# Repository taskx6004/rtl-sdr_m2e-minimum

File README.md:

# rtl-sdr_m2e-minimum
Minimum hardware design for RTL-SDR in m.2 key-e form

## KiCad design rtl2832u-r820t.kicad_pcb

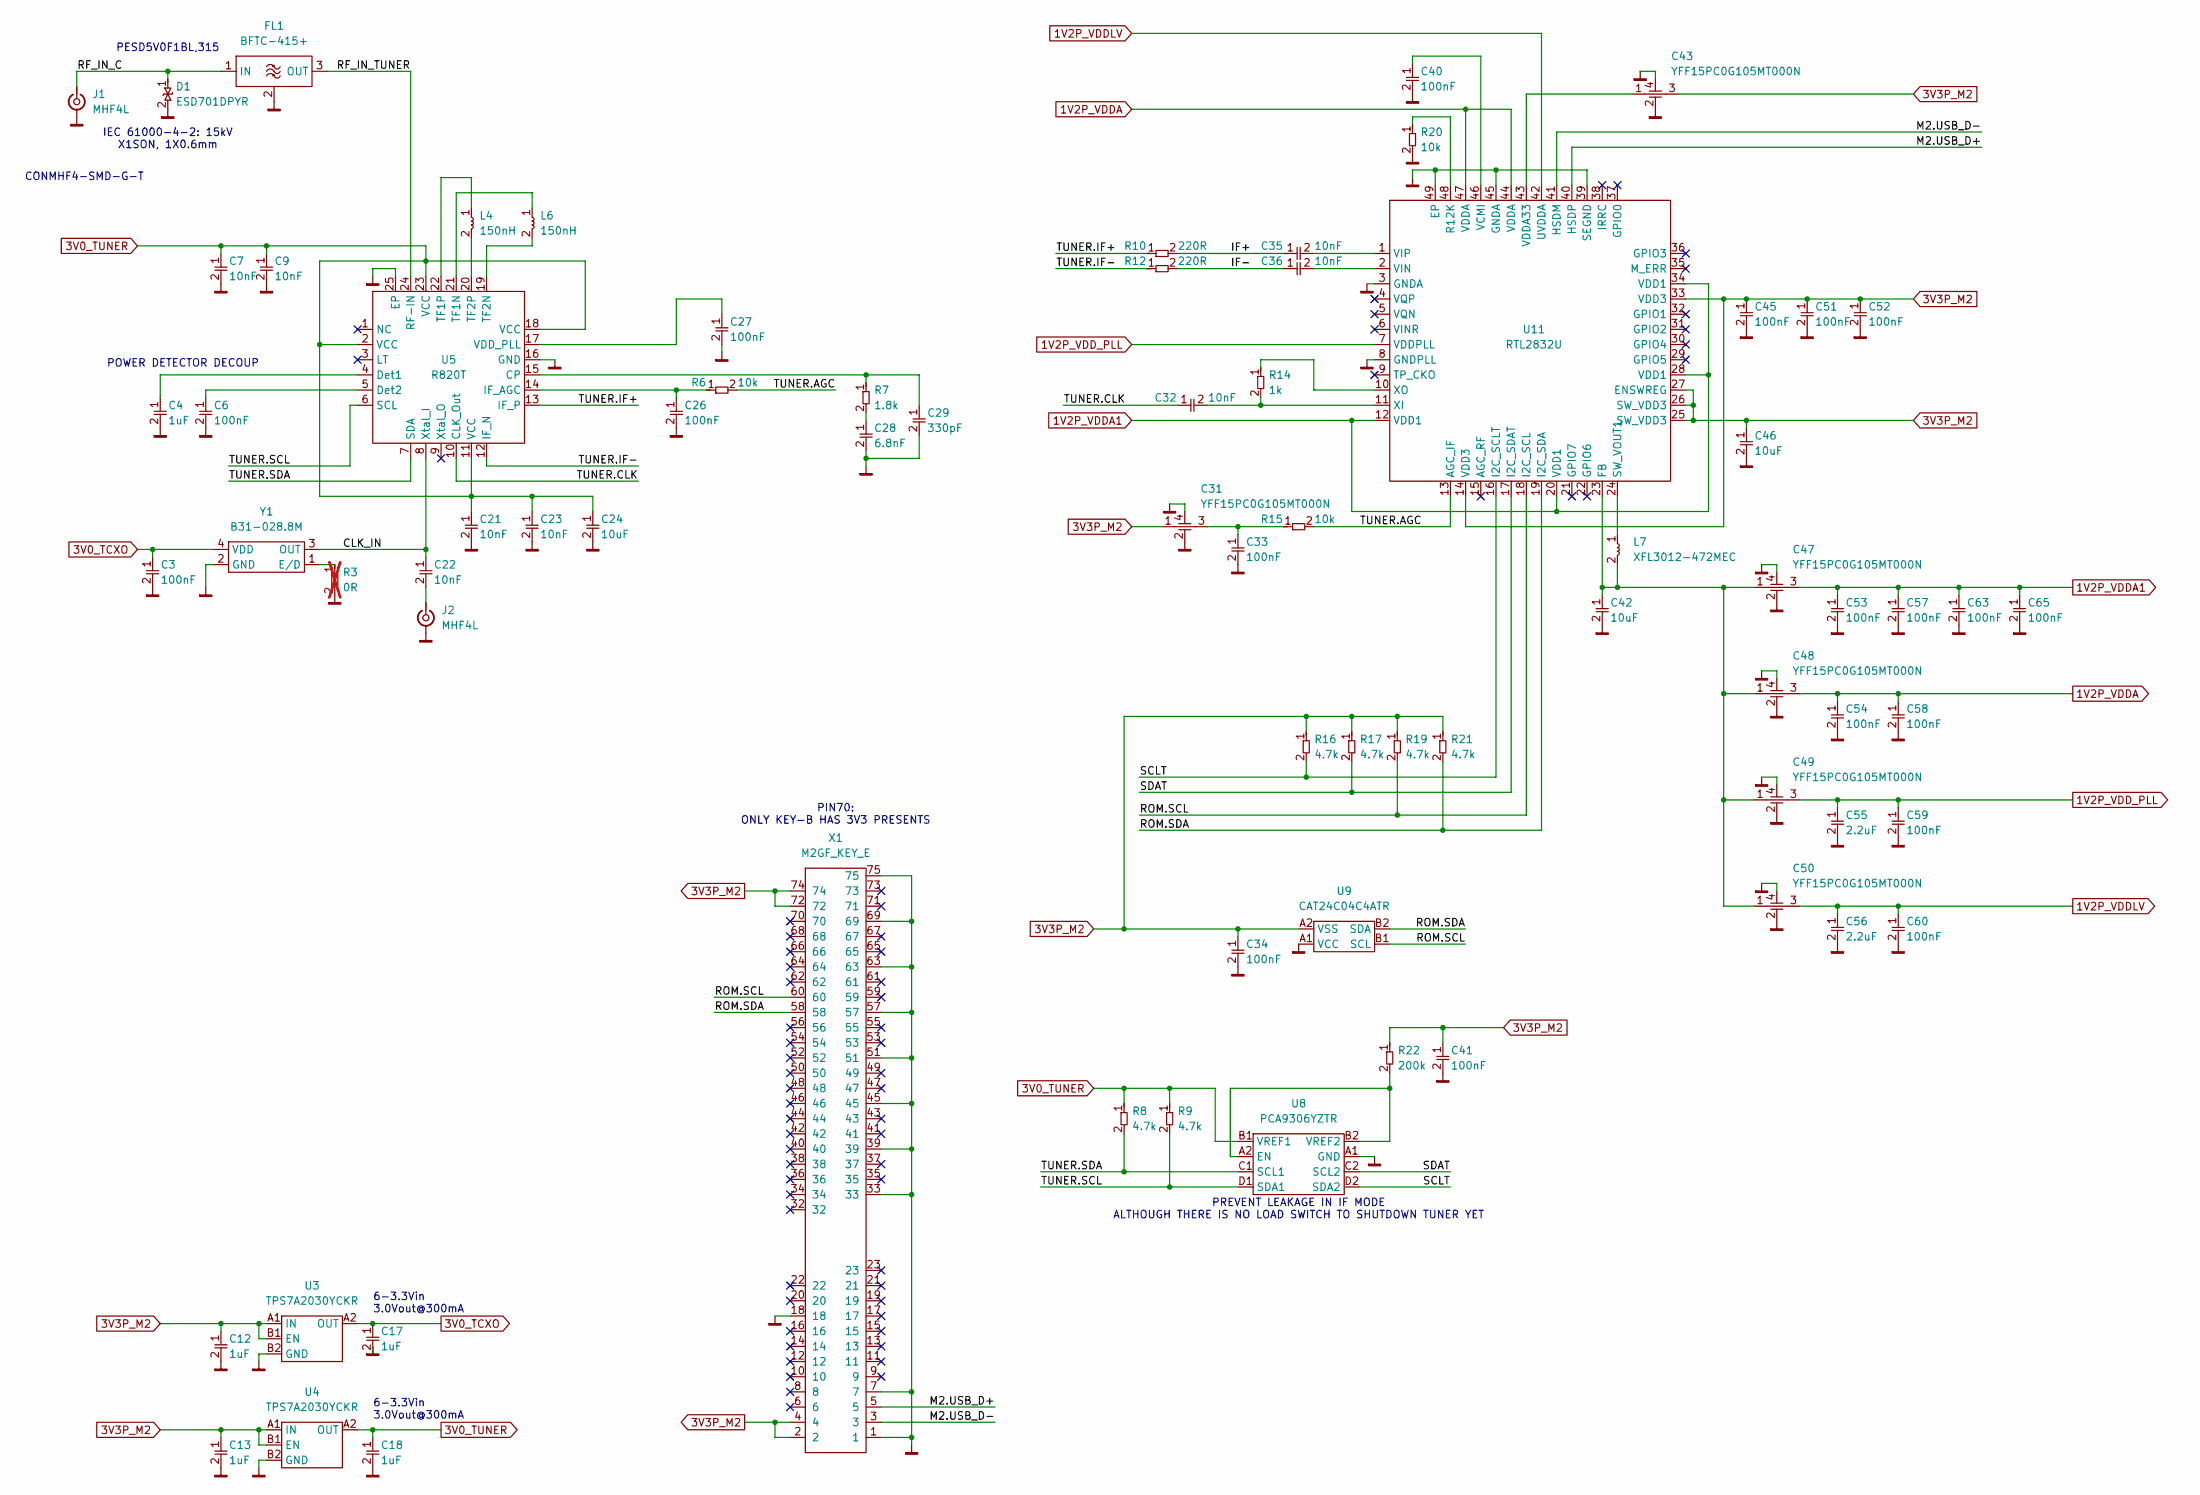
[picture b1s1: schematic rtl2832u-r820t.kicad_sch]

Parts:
C3, C6, C26, C27, C33, C34, C40, C41, C45, C51, C52, C53, C54, C57, C58, C59, C60, C63, C65: 100nF; C_0201
C4, C12, C13, C17, C18: 1uF; C_0201
C7, C9, C21, C22, C23, C32, C35, C36: 10nF; C_0201
C24, C42, C46: 10uF; C_0402
C28: 6.8nF; C_0201
C29: 330pF; C_0201
C31, C43, C47, C48, C49, C50: YFF15PC0G105MT000N
C55, C56: 2.2uF; C_0402
D1: ESD701DPYR
FL1: BFTC-415+
J1, J2: MHF4L
L4, L6: 150nH; L_0402
L7: XFL3012-472MEC
R3: 0R; R_0201; not fitted
R6, R15, R20: 10k; R_0201
R7: 1.8k; R_0201
R8, R9, R16, R17, R19, R21: 4.7k; R_0201
R10, R12: 220R; R_0201
R14: 1k; R_0201
R22: 200k; R_0201
U3, U4: TPS7A2030YCKR; TPS7A2018PYCKR
U5: R820T; R820T2
U8: PCA9306YZTR
U9: CAT24C04C4ATR; SN74LVC1G06DSFR
U11: RTL2832U
X1: M2GF_KEY_E; M2GF_KEY_E_2230
Y1: B31-028.8M; DSB221SDN

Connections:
1V2P_VDDA: C48.3, C54.1, C58.1, U11.44 (VDDA), U11.47 (VDDA)
1V2P_VDDA1: C47.3, C53.1, C57.1, C63.1, C65.1, U11.12 (VDD1), U11.20 (VDD1), U11.28 (VDD1), U11.34 (VDD1)
1V2P_VDDLV: C50.3, C56.1, C60.1, U11.42 (UVDDA)
1V2P_VDD_PLL: C49.3, C55.1, C59.1, U11.7 (VDDPLL)
3V0_TCXO: C3.1, C17.1, U3.A2 (OUT), Y1.4 (VDD)
3V0_TUNER: C7.1, C9.1, C18.1, C21.1, C23.1, C24.1, R8.1, R9.1, U4.A2 (OUT), U5.2 (VCC), U5.11 (VCC), U5.18 (VCC), U5.23 (VCC), U8.B1 (VREF1)
3V3P_M2: C12.1, C13.1, C31.1, C34.1, C41.1, C43.3, C45.1, C46.1, C51.1, C52.1, R16.1, R17.1, R19.1, R21.1, R22.1, U3.A1 (IN), U3.B1 (EN), U4.A1 (IN), U4.B1 (EN), U9.A2 (VSS), U11.14 (VDD3), U11.25 (SW_VDD3), U11.26 (SW_VDD3), U11.27 (ENSWREG), U11.33 (VDD3), X1.2, X1.4, X1.72, X1.74
/CLK_IN: C22.1, U5.8 (Xtal_I), Y1.3 (OUT)
/IF+: C35.1, R10.2
/IF-: C36.1, R12.2
/M2.USB_D+: U11.40 (HSDP), X1.5
/M2.USB_D-: U11.41 (HSDM), X1.3
/RF_IN_C: D1.1, FL1.1 (IN), J1.1 (In)
/RF_IN_TUNER: FL1.3 (OUT), U5.24 (RF-IN)
/ROM.SCL: R19.2, U9.B1 (SCL), U11.18 (I2C_SCL), X1.60
/ROM.SDA: R21.2, U9.B2 (SDA), U11.19 (I2C_SDA), X1.58
/SCLT: R16.2, U8.D2 (SDA2), U11.16 (I2C_SCLT)
/SDAT: R17.2, U8.C2 (SCL2), U11.17 (I2C_SDAT)
/TUNER.AGC: R6.2, R15.2, U11.13 (AGC_IF)
/TUNER.CLK: C32.1, U5.10 (CLK_Out)
/TUNER.IF+: R10.1, U5.13 (IF_P)
/TUNER.IF-: R12.1, U5.12 (IF_N)
/TUNER.SCL: R9.2, U5.6 (SCL), U8.D1 (SDA1)
/TUNER.SDA: R8.2, U5.7 (SDA), U8.C1 (SCL1)
GND: C3.2, C4.2, C6.2, C7.2, C9.2, C12.2, C13.2, C17.2, C18.2, C21.2, C23.2, C24.2, C26.2, C27.2, C28.2, C29.2, C31.2, C31.4, C33.2, C34.2, C40.2, C41.2, C42.2, C43.2, C43.4, C45.2, C46.2, C47.2, C47.4, C48.2, C48.4, C49.2, C49.4, C50.2, C50.4, C51.2, C52.2, C53.2, C54.2, C55.2, C56.2, C57.2, C58.2, C59.2, C60.2, C63.2, C65.2, D1.2, FL1.2 (GND), J1.2 (Ext), J2.2 (Ext), R3.2, R20.2, U3.B2 (GND), U4.B2 (GND), U5.16 (GND), U5.25 (EP), U8.A1 (GND), U9.A1 (VCC), U11.3 (GNDA), U11.8 (GNDPLL), U11.39 (SEGND), U11.45 (GNDA), U11.49 (EP), X1.1, X1.7, X1.18, X1.33, X1.39, X1.45, X1.51, X1.57, X1.63, X1.69, X1.75, Y1.2 (GND)
unnamed: C28.1, R7.2
unnamed: C31.3, C33.1, R15.1
unnamed: C22.2, J2.1 (In)
unnamed: C29.1, R7.1, U5.15 (CP)
unnamed: C4.1, U5.4 (Det1)
unnamed: C6.1, U5.5 (Det2)
unnamed: C26.1, R6.1, U5.14 (IF_AGC)
unnamed: L6.1, U5.21 (TF1N)
unnamed: L4.1, U5.22 (TF1P)
unnamed: L6.2, U5.19 (TF2N)
unnamed: L4.2, U5.20 (TF2P)
unnamed: C27.1, U5.17 (VDD_PLL)
unnamed: R22.2, U8.A2 (EN), U8.B2 (VREF2)
unnamed: C42.1, C47.1, C48.1, C49.1, C50.1, L7.2, U11.23 (FB)
unnamed: R20.1, U11.48 (R12K)
unnamed: L7.1, U11.24 (SW_VOUT1)
unnamed: C40.1, U11.46 (VCMI)
unnamed: C43.1, U11.43 (VDDA33)
unnamed: C36.2, U11.2 (VIN)
unnamed: C35.2, U11.1 (VIP)
unnamed: C32.2, R14.2, U11.11 (XI)
unnamed: R14.1, U11.10 (XO)
unnamed: R3.1, Y1.1 (E/D)

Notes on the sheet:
6-3.3Vin 3.0Vout@300mA
PREVENT LEAKAGE IN IF MODE ALTHOUGH THERE IS NO LOAD SWITCH TO SHUTDOWN TUNER YET
IEC 61000-4-2: 15kV X1SON, 1X0.6mm
PESD5V0F1BL,315
PIN70: ONLY KEY-B HAS 3V3 PRESENTS
POWER DETECTOR DECOUP
CONMHF4-SMD-G-T

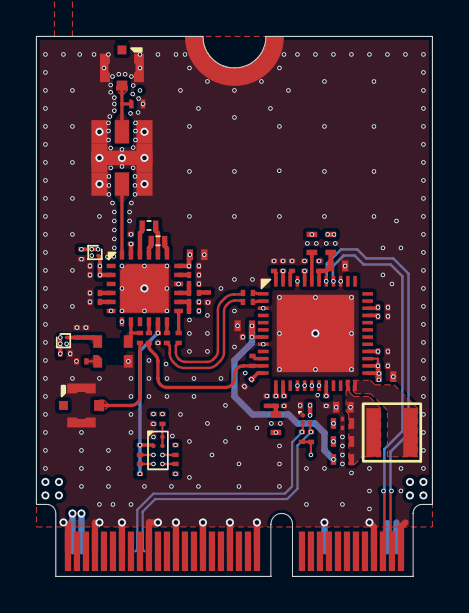
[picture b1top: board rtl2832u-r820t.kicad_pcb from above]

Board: 6 copper layers, 22.0 x 30.0 mm, 75 parts (0 on the bottom side), 48 nets.

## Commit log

2025-05-27 initial upload
